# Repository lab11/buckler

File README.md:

Berkeley Buckler-ext
================

This is a fork of https://github.com/lab11/buckler

It changes Board makefiles to support https://github.com/gestalt-arch/gestalt-arch

It also extends the i2c implementation to support a lidar sensor via SC16IS750 I2C/SPI to UART Bridge Module from sandboxelectronics.com

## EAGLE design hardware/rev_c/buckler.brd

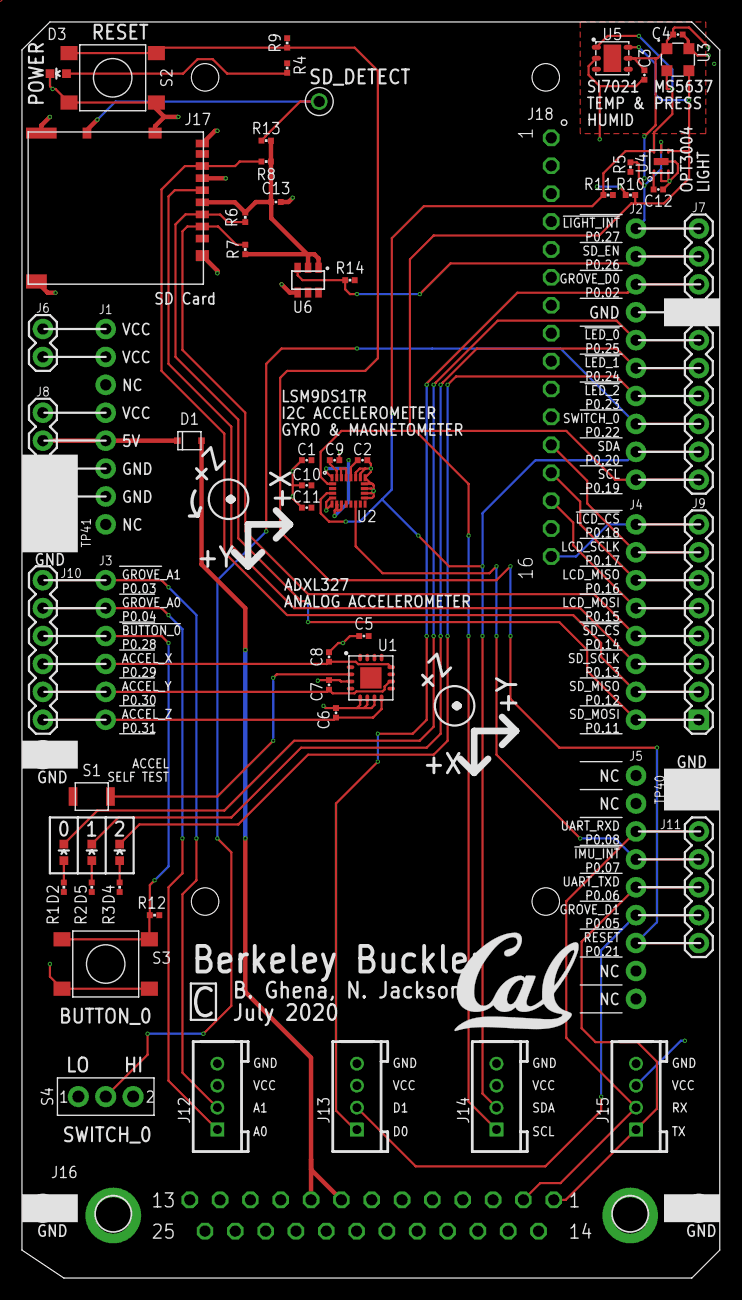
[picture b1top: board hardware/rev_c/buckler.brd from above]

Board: 2 copper layers, 63.5 x 114.3 mm, 63 parts (0 on the bottom side), 41 nets.

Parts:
C1, C2: 10nF; 0402_CAP
C3, C4, C5, C6, C7, C8, C9, C10, C11, C12: 100nF; 0402_CAP
C13: 4.7uF; 0402_CAP
D1: SOD323
D2: RED; LED-0603
D3: GREEN; LED-0603
D4: BLUE; LED-0603
D5: YELLOW; LED-0603
J1: NRF52832DK_SHIELD
J6: 1X02
J7: M10"; 1X10
J8: 1X04
J9: 1X08
J10: 1X06
J11: 1X05
J12, J13, J14, J15: HW4-2.0
J16: DB25_5747846
J17: DM3AT-SF-PEJM5
J18: NHD-0216KZWSERIAL; NHD-0216KZW
R1, R2, R3, R4: 1k; 0402_RES
R5, R6, R7, R8, R9, R10, R11, R12: 10k; 0402_RES
R13, R14: 100k; 0402_RES
S1: B3U-1000P
S2, S3: PTS645SM43SMTR92; PTS645
S4: TE_SSA12/SPDT
TP35, TP36, TP37, TP38: TEST_POINT_0.040IN; TESTPOINT_0.040IN
TP40, TP41: TEST_POINT_0.078IN; TESTPOINT_0.078IN
U1: ADXL327; LFCSP-16
U2: LSM9DS1TR; LGA-24_3X3P5X1_STM
U3: MS5637-02BA03; 4-SMD
U4: OPT3004DNPR; DNP0006A
U5: SI7021-A20-GM1; DFN-6/3MM
U6: SIP32510; TSOT23-6
U$5: UCB_CAL_350MIL

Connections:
5V_IN: D1.P$2, J16.8, J16.9
!BUTTON_0: J1.P0.28, J10.4, R12.1, S3.1, S3.2
!IMU_INTERRUPT: J1.P0.07, J11.4, U2.11
!LCD_CS: J1.P0.18, J9.8, J18.16
!LED_0: D2.C, J1.P0.25, J7.5
!LED_1: D5.C, J1.P0.24, J7.6
!LED_2: D4.C, J1.P0.23, J7.7
!LIGHT_INTERRUPT: J1.P0.27, J7.1, R5.1, U4.5
!RESET: J1.P0.21, J11.1, R9.1, S2.1, S2.2
!SD_CS: J1.P0.14, J9.4, J17.2, R7.1
!SD_DETECT: J17.A, R13.1, TP38.TESTPOINT
+3V3: C1.2, C3.1, C4.1, C5.1, C10.2, C11.2, C12.1, J1.3.3V@0, J1.3.3V@1, J1.3.3V@2, J6.1, J6.2, J8.4, J12.3, J13.3, J14.3, J15.3, J18.2, R1.1, R2.1, R3.1, R4.1, R5.2, R9.2, R10.2, R11.2, R12.2, R14.2, S1.2, S4.2, U1.14, U1.15, U2.1, U2.3, U2.7, U2.8, U2.22, U2.23, U3.1, U4.1, U5.5, U6.5, U6.6
+5V: D1.P$1, J1.5V, J8.3
ANALOG_ACCEL_X: C8.1, J1.P0.29, J10.3, U1.12
ANALOG_ACCEL_Y: C7.1, J1.P0.30, J10.2, U1.10
ANALOG_ACCEL_Z: C6.1, J1.P0.31, J10.1, U1.8
GND: C1.1, C2.1, C3.2, C4.2, C5.2, C6.2, C7.2, C8.2, C9.2, C10.1, C11.1, C12.2, C13.2, D3.C, J1.GND@0, J1.GND@1, J1.GND@2, J7.4, J8.1, J8.2, J12.4, J13.4, J14.4, J15.4, J16.6, J16.16, J16.20, J16.21, J16.24, J16.25, J17.6, J17.B, J17.MOUNT0, J17.MOUNT1, J17.MOUNT2, J17.MOUNT3, J18.1, S2.3, S2.4, S3.3, S3.4, S4.1, TP35.TESTPOINT, TP36.TESTPOINT, TP37.TESTPOINT, TP40.1, TP41.1, U1.3, U1.5, U1.6, U1.7, U2.5, U2.6, U2.14, U2.15, U2.16, U2.17, U2.18, U2.19, U2.20, U3.4, U4.2, U4.3, U4.7, U5.2, U6.4
GROVE_A0: J1.P0.04, J10.5, J12.1
GROVE_A1: J1.P0.03, J10.6, J12.2
GROVE_D0: J1.P0.02, J7.3, J13.1
GROVE_D1: J1.P0.05, J11.2, J13.2
LCD_MISO: J1.P0.16, J9.6, J18.13
LCD_MOSI: J1.P0.15, J9.5, J18.14
LCD_SCLK: J1.P0.17, J9.7, J18.12
unnamed: C9.1, U2.24
unnamed: D3.A, R4.2
unnamed: D4.A, R3.2
unnamed: D5.A, R2.2
unnamed: C2.2, U2.21
unnamed: S1.1, U1.2
unnamed: C13.1, J17.4, R6.2, R7.2, R8.2, R13.2, U6.1, U6.2
unnamed: D2.A, R1.2
SD_ENABLE: J1.P0.26, J7.2, R14.1, U6.3
SD_MISO: J1.P0.12, J9.2, J17.7, R8.1
SD_MOSI: J1.P0.11, J9.1, J17.3, R6.1
SD_SCLK: J1.P0.13, J9.3, J17.5
SENSORS_SCL: J1.P0.19, J7.10, J14.1, R10.1, U2.2, U3.3, U4.4, U5.6
SENSORS_SDA: J1.P0.20, J7.9, J14.2, R11.1, U2.4, U3.2, U4.6, U5.1
SWITCH_0: J1.P0.22, J7.8, S4.IN
UART_RX: J1.P0.08, J11.5, J15.2, J16.2
UART_TX: J1.P0.06, J11.3, J15.1, J16.1

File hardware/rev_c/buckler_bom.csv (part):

# Bill of Materials,,,,,,,,,,,,,,,,,,,,,,,,,,,,,,,,,,,,,,,,,,,,,,,,,,,,,,,,,,,,,,,,,,,,,,,,,,,,,,,,,,,,,,,,,,,,,,,,,,,,,,,,,,,,,,,,,,,,,,,,,,,,,,,,,,,,,,,,,,,,,,,,,,,,,,,,,,,,,,,,,,,,,,,,,,,,,,,,,,,,,,,,,,,,,,,,,,,,,,,,,,,,,,,,,,,,,,,,,,,,,,,,,,,,,,,,,,,,,,,,,,,,,,,,,,,,,,,,,,,,,,,,,,,,,,,,,,,,,,,,,,,,,,,,,,,,,,,,,,,,,,,,,,,,,,,,,,,,,,,,,,,,,,,,,,,,,,,,,,,,,,,,,,,,,,,,,,,,,,,,,,,,,,,,,,,,,,,,,,,,,,,,,,,,,,,,,,,,,,,,,,,,,,,,,,,,,,,,,,,,,,,,,,,,,,,,,,,,,,,,,,,,,,,,,,,,,,,,,,,,,,,,,,,,,,,,,,,,,,,,,,,,,,,,,,,,,,,,,,,,,,,,,,,,,,,,,,,,,,,,,,,,,,,,,,,,,,,,,,,,,,,,,,,,,,,,,,,,,,,,,,,,,,,,,,,,,,,,,,,,,,,,,,,,,,,,,,,,,,,,,,,,,,,,,,,,,,,,,,,,,,,,,,,,,,,,,,,,,,,,,,,,,,,,,,,,,,,,,,,,,,,,,,,,,,,,,,,,,,,,,,,,,,,,,,,,,,,,,,,,,,,,,,,,,,,,,,,,,,,,,,,,,,,,,,,,,,,,,,,,,,,,,,,,,,,,,,,,,,,,,,,,,,,,,,,,,,,,,,,,,,,,,,,,,,,,,,,,,,,,,,,,,,,,,,,,,,,,,,,,,,,,,,,,,,,,,,,,,,,,,,,,,,,,,,,,,,,,,,,,,,,,,,,,,,,,,,,,,,,,,,,,,,,,,,,,,,,,,,,,,,,,,,,,,,,,,,,,,,,,,,,,,,,,,,,,,,,,,,,,,,,,,,,,,,,,,,,,,,,,,,,,,,,,,,,,,,,,,,,,,,,,,,,,,,,,,,,,,,,,,,,,,,,,,,,,,,,,,,,,,,,
# Converted from {},,,,,,,,,,,,,,,,,,,,,,,,,,,,,,,,,,,,,,,,,,,,,,,,,,,,,,,,,,,,,,,,,,,,,,,,,,,,,,,,,,,,,,,,,,,,,,,,,,,,,,,,,,,,,,,,,,,,,,,,,,,,,,,,,,,,,,,,,,,,,,,,,,,,,,,,,,,,,,,,,,,,,,,,,,,,,,,,,,,,,,,,,,,,,,,,,,,,,,,,,,,,,,,,,,,,,,,,,,,,,,,,,,,,,,,,,,,,,,,,,,,,,,,,,,,,,,,,,,,,,,,,,,,,,,,,,,,,,,,,,,,,,,,,,,,,,,,,,,,,,,,,,,,,,,,,,,,,,,,,,,,,,,,,,,,,,,,,,,,,,,,,,,,,,,,,,,,,,,,,,,,,,,,,,,,,,,,,,,,,,,,,,,,,,,,,,,,,,,,,,,,,,,,,,,,,,,,,,,,,,,,,,,,,,,,,,,,,,,,,,,,,,,,,,,,,,,,,,,,,,,,,,,,,,,,,,,,,,,,,,,,,,,,,,,,,,,,,,,,,,,,,,,,,,,,,,,,,,,,,,,,,,,,,,,,,,,,,,,,,,,,,,,,,,,,,,,,,,,,,,,,,,,,,,,,,,,,,,,,,,,,,,,,,,,,,,,,,,,,,,,,,,,,,,,,,,,,,,,,,,,,,,,,,,,,,,,,,,,,,,,,,,,,,,,,,,,,,,,,,,,,,,,,,,,,,,,,,,,,,,,,,,,,,,,,,,,,,,,,,,,,,,,,,,,,,,,,,,,,,,,,,,,,,,,,,,,,,,,,,,,,,,,,,,,,,,,,,,,,,,,,,,,,,,,,,,,,,,,,,,,,,,,,,,,,,,,,,,,,,,,,,,,,,,,,,,,,,,,,,,,,,,,,,,,,,,,,,,,,,,,,,,,,,,,,,,,,,,,,,,,,,,,,,,,,,,,,,,,,,,,,,,,,,,,,,,,,,,,,,,,,,,,,,,,,,,,,,,,,,,,,,,,,,,,,,,,,,,,,,,,,,,,,,,,,,,,,,,,,,,,,,,,,,,,,,,,,,,,,,,,,,,,,,,,,,,,,,,,,,,,,,,,,,,,,,,,,,,,,,,,,
# Generated by bom_to_text.py,,,,,,,,,,,,,,,,,,,,,,,,,,,,,,,,,,,,,,,,,,,,,,,,,,,,,,,,,,,,,,,,,,,,,,,,,,,,,,,,,,,,,,,,,,,,,,,,,,,,,,,,,,,,,,,,,,,,,,,,,,,,,,,,,,,,,,,,,,,,,,,,,,,,,,,,,,,,,,,,,,,,,,,,,,,,,,,,,,,,,,,,,,,,,,,,,,,,,,,,,,,,,,,,,,,,,,,,,,,,,,,,,,,,,,,,,,,,,,,,,,,,,,,,,,,,,,,,,,,,,,,,,,,,,,,,,,,,,,,,,,,,,,,,,,,,,,,,,,,,,,,,,,,,,,,,,,,,,,,,,,,,,,,,,,,,,,,,,,,,,,,,,,,,,,,,,,,,,,,,,,,,,,,,,,,,,,,,,,,,,,,,,,,,,,,,,,,,,,,,,,,,,,,,,,,,,,,,,,,,,,,,,,,,,,,,,,,,,,,,,,,,,,,,,,,,,,,,,,,,,,,,,,,,,,,,,,,,,,,,,,,,,,,,,,,,,,,,,,,,,,,,,,,,,,,,,,,,,,,,,,,,,,,,,,,,,,,,,,,,,,,,,,,,,,,,,,,,,,,,,,,,,,,,,,,,,,,,,,,,,,,,,,,,,,,,,,,,,,,,,,,,,,,,,,,,,,,,,,,,,,,,,,,,,,,,,,,,,,,,,,,,,,,,,,,,,,,,,,,,,,,,,,,,,,,,,,,,,,,,,,,,,,,,,,,,,,,,,,,,,,,,,,,,,,,,,,,,,,,,,,,,,,,,,,,,,,,,,,,,,,,,,,,,,,,,,,,,,,,,,,,,,,,,,,,,,,,,,,,,,,,,,,,,,,,,,,,,,,,,,,,,,,,,,,,,,,,,,,,,,,,,,,,,,,,,,,,,,,,,,,,,,,,,,,,,,,,,,,,,,,,,,,,,,,,,,,,,,,,,,,,,,,,,,,,,,,,,,,,,,,,,,,,,,,,,,,,,,,,,,,,,,,,,,,,,,,,,,,,,,,,,,,,,,,,,,,,,,,,,,,,,,,,,,,,,,,,,,,,,,,,,,,,,,,,,,,,,,,,,,,,,,,,,,,,,,,,,,,,,,,,
#,,,,,,,,,,,,,,,,,,,,,,,,,,,,,,,,,,,,,,,,,,,,,,,,,,,,,,,,,,,,,,,,,,,,,,,,,,,,,,,,,,,,,,,,,,,,,,,,,,,,,,,,,,,,,,,,,,,,,,,,,,,,,,,,,,,,,,,,,,,,,,,,,,,,,,,,,,,,,,,,,,,,,,,,,,,,,,,,,,,,,,,,,,,,,,,,,,,,,,,,,,,,,,,,,,,,,,,,,,,,,,,,,,,,,,,,,,,,,,,,,,,,,,,,,,,,,,,,,,,,,,,,,,,,,,,,,,,,,,,,,,,,,,,,,,,,,,,,,,,,,,,,,,,,,,,,,,,,,,,,,,,,,,,,,,,,,,,,,,,,,,,,,,,,,,,,,,,,,,,,,,,,,,,,,,,,,,,,,,,,,,,,,,,,,,,,,,,,,,,,,,,,,,,,,,,,,,,,,,,,,,,,,,,,,,,,,,,,,,,,,,,,,,,,,,,,,,,,,,,,,,,,,,,,,,,,,,,,,,,,,,,,,,,,,,,,,,,,,,,,,,,,,,,,,,,,,,,,,,,,,,,,,,,,,,,,,,,,,,,,,,,,,,,,,,,,,,,,,,,,,,,,,,,,,,,,,,,,,,,,,,,,,,,,,,,,,,,,,,,,,,,,,,,,,,,,,,,,,,,,,,,,,,,,,,,,,,,,,,,,,,,,,,,,,,,,,,,,,,,,,,,,,,,,,,,,,,,,,,,,,,,,,,,,,,,,,,,,,,,,,,,,,,,,,,,,,,,,,,,,,,,,,,,,,,,,,,,,,,,,,,,,,,,,,,,,,,,,,,,,,,,,,,,,,,,,,,,,,,,,,,,,,,,,,,,,,,,,,,,,,,,,,,,,,,,,,,,,,,,,,,,,,,,,,,,,,,,,,,,,,,,,,,,,,,,,,,,,,,,,,,,,,,,,,,,,,,,,,,,,,,,,,,,,,,,,,,,,,,,,,,,,,,,,,,,,,,,,,,,,,,,,,,,,,,,,,,,,,,,,,,,,,,,,,,,,,,,,,,,,,,,,,,,,,,,,,,,,,,,,,,,,,,,,,,,,,,,,,,,,,,,,,,,,,,,,,,,,,,,,,,,
,,,,,,,,,,,,,,,,,,,,,,,,,,,,,,,,,,,,,,,,,,,,,,,,,,,,,,,,,,,,,,,,,,,,,,,,,,,,,,,,,,,,,,,,,,,,,,,,,,,,,,,,,,,,,,,,,,,,,,,,,,,,,,,,,,,,,,,,,,,,,,,,,,,,,,,,,,,,,,,,,,,,,,,,,,,,,,,,,,,,,,,,,,,,,,,,,,,,,,,,,,,,,,,,,,,,,,,,,,,,,,,,,,,,,,,,,,,,,,,,,,,,,,,,,,,,,,,,,,,,,,,,,,,,,,,,,,,,,,,,,,,,,,,,,,,,,,,,,,,,,,,,,,,,,,,,,,,,,,,,,,,,,,,,,,,,,,,,,,,,,,,,,,,,,,,,,,,,,,,,,,,,,,,,,,,,,,,,,,,,,,,,,,,,,,,,,,,,,,,,,,,,,,,,,,,,,,,,,,,,,,,,,,,,,,,,,,,,,,,,,,,,,,,,,,,,,,,,,,,,,,,,,,,,,,,,,,,,,,,,,,,,,,,,,,,,,,,,,,,,,,,,,,,,,,,,,,,,,,,,,,,,,,,,,,,,,,,,,,,,,,,,,,,,,,,,,,,,,,,,,,,,,,,,,,,,,,,,,,,,,,,,,,,,,,,,,,,,,,,,,,,,,,,,,,,,,,,,,,,,,,,,,,,,,,,,,,,,,,,,,,,,,,,,,,,,,,,,,,,,,,,,,,,,,,,,,,,,,,,,,,,,,,,,,,,,,,,,,,,,,,,,,,,,,,,,,,,,,,,,,,,,,,,,,,,,,,,,,,,,,,,,,,,,,,,,,,,,,,,,,,,,,,,,,,,,,,,,,,,,,,,,,,,,,,,,,,,,,,,,,,,,,,,,,,,,,,,,,,,,,,,,,,,,,,,,,,,,,,,,,,,,,,,,,,,,,,,,,,,,,,,,,,,,,,,,,,,,,,,,,,,,,,,,,,,,,,,,,,,,,,,,,,,,,,,,,,,,,,,,,,,,,,,,,,,,,,,,,,,,,,,,,,,,,,,,,,,,,,,,,,,,,,,,,,,,,,,,,,,,,,,,,,,,,,,,,,,,,,,,,,,,,,,,,,,,,,,,,,,,,,,
Qty,Value,Device,Package,Parts,Description,DESCRIPTION,DIGIKEY,MANUFACTURER,MOUSER,MPN,,,,,,,,,,,,,,,,,,,,,,,,,,,,,,,,,,,,,,,,,,,,,,,,,,,,,,,,,,,,,,,,,,,,,,,,,,,,,,,,,,,,,,,,,,,,,,,,,,,,,,,,,,,,,,,,,,,,,,,,,,,,,,,,,,,,,,,,,,,,,,,,,,,,,,,,,,,,,,,,,,,,,,,,,,,,,,,,,,,,,,,,,,,,,,,,,,,,,,,,,,,,,,,,,,,,,,,,,,,,,,,,,,,,,,,,,,,,,,,,,,,,,,,,,,,,,,,,,,,,,,,,,,,,,,,,,,,,,,,,,,,,,,,,,,,,,,,,,,,,,,,,,,,,,,,,,,,,,,,,,,,,,,,,,,,,,,,,,,,,,,,,,,,,,,,,,,,,,,,,,,,,,,,,,,,,,,,,,,,,,,,,,,,,,,,,,,,,,,,,,,,,,,,,,,,,,,,,,,,,,,,,,,,,,,,,,,,,,,,,,,,,,,,,,,,,,,,,,,,,,,,,,,,,,,,,,,,,,,,,,,,,,,,,,,,,,,,,,,,,,,,,,,,,,,,,,,,,,,,,,,,,,,,,,,,,,,,,,,,,,,,,,,,,,,,,,,,,,,,,,,,,,,,,,,,,,,,,,,,,,,,,,,,,,,,,,,,,,,,,,,,,,,,,,,,,,,,,,,,,,,,,,,,,,,,,,,,,,,,,,,,,,,,,,,,,,,,,,,,,,,,,,,,,,,,,,,,,,,,,,,,,,,,,,,,,,,,,,,,,,,,,,,,,,,,,,,,,,,,,,,,,,,,,,,,,,,,,,,,,,,,,,,,,,,,,,,,,,,,,,,,,,,,,,,,,,,,,,,,,,,,,,,,,,,,,,,,,,,,,,,,,,,,,,,,,,,,,,,,,,,,,,,,,,,,,,,,,,,,,,,,,,,,,,,,,,,,,,,,,,,,,,,,,,,,,,,,,,,,,,,,,,,,,,,,,,,,,,,,,,,,,,,,,,,,,,,,,,,,,,,,,,,,,,,,,,,,,,,,,,,,,,,,,,,,,,,,,,,,,,,,,,,,,,,,,,,,,,,,,,,,,,,,,,,,,,,,,,,,,,,,,,,,,,,,,,
1,,DIODE_SCHOTTKYSOD323,SOD323,D1,,DIODE SCHOTTKY 30V 500MA SOD323,B0530WS-FDICT-ND,Diodes Incorporated,,B0530WS-7-F,,,,,,,,,,,,,,,,,,,,,,,,,,,,,,,,,,,,,,,,,,,,,,,,,,,,,,,,,,,,,,,,,,,,,,,,,,,,,,,,,,,,,,,,,,,,,,,,,,,,,,,,,,,,,,,,,,,,,,,,,,,,,,,,,,,,,,,,,,,,,,,,,,,,,,,,,,,,,,,,,,,,,,,,,,,,,,,,,,,,,,,,,,,,,,,,,,,,,,,,,,,,,,,,,,,,,,,,,,,,,,,,,,,,,,,,,,,,,,,,,,,,,,,,,,,,,,,,,,,,,,,,,,,,,,,,,,,,,,,,,,,,,,,,,,,,,,,,,,,,,,,,,,,,,,,,,,,,,,,,,,,,,,,,,,,,,,,,,,,,,,,,,,,,,,,,,,,,,,,,,,,,,,,,,,,,,,,,,,,,,,,,,,,,,,,,,,,,,,,,,,,,,,,,,,,,,,,,,,,,,,,,,,,,,,,,,,,,,,,,,,,,,,,,,,,,,,,,,,,,,,,,,,,,,,,,,,,,,,,,,,,,,,,,,,,,,,,,,,,,,,,,,,,,,,,,,,,,,,,,,,,,,,,,,,,,,,,,,,,,,,,,,,,,,,,,,,,,,,,,,,,,,,,,,,,,,,,,,,,,,,,,,,,,,,,,,,,,,,,,,,,,,,,,,,,,,,,,,,,,,,,,,,,,,,,,,,,,,,,,,,,,,,,,,,,,,,,,,,,,,,,,,,,,,,,,,,,,,,,,,,,,,,,,,,,,,,,,,,,,,,,,,,,,,,,,,,,,,,,,,,,,,,,,,,,,,,,,,,,,,,,,,,,,,,,,,,,,,,,,,,,,,,,,,,,,,,,,,,,,,,,,,,,,,,,,,,,,,,,,,,,,,,,,,,,,,,,,,,,,,,,,,,,,,,,,,,,,,,,,,,,,,,,,,,,,,,,,,,,,,,,,,,,,,,,,,,,,,,,,,,,,,,,,,,,,,,,,,,,,,,,,,,,,,,,,,,,,,,,,,,,,,,,,,,,,,,,,,,,,,,,,,,,,,,,,,,,,,,,,,,,,,,,,,,,,,,,,,,,,,,,,,,,,,,,,,,,,,,,,,,,,,,,,,,,,,
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
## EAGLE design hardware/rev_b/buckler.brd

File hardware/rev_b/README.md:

Hardware Files
==============

The Berkeley Buckler was created in
[Eagle](https://www.autodesk.com/products/eagle/overview) and the `buckler.sch`
and `buckler.brd` files are Eagle schematic and board files respectively.
Schematic and board files can be viewed without Eagle in `buckler.pdf`.
`buckler_bom.xlsx` is the Bill of Materials (list of parts). It is also
provided as `txt` and `csv` files for convenience.

## Changes from prior revision
 * Change base board from the nRF52840DK to the nRF52DK (based on the nRF52832) due to availability
     * Reduced number of buttons, switches, and grove headers to deal with reduced number of pins
     * Removed connection to SD card detect signal to deal with reduced number of pins
     * Re-mapped signals to development kit pins
 * Made text bigger and added more test points
 * Shrunk board size a little

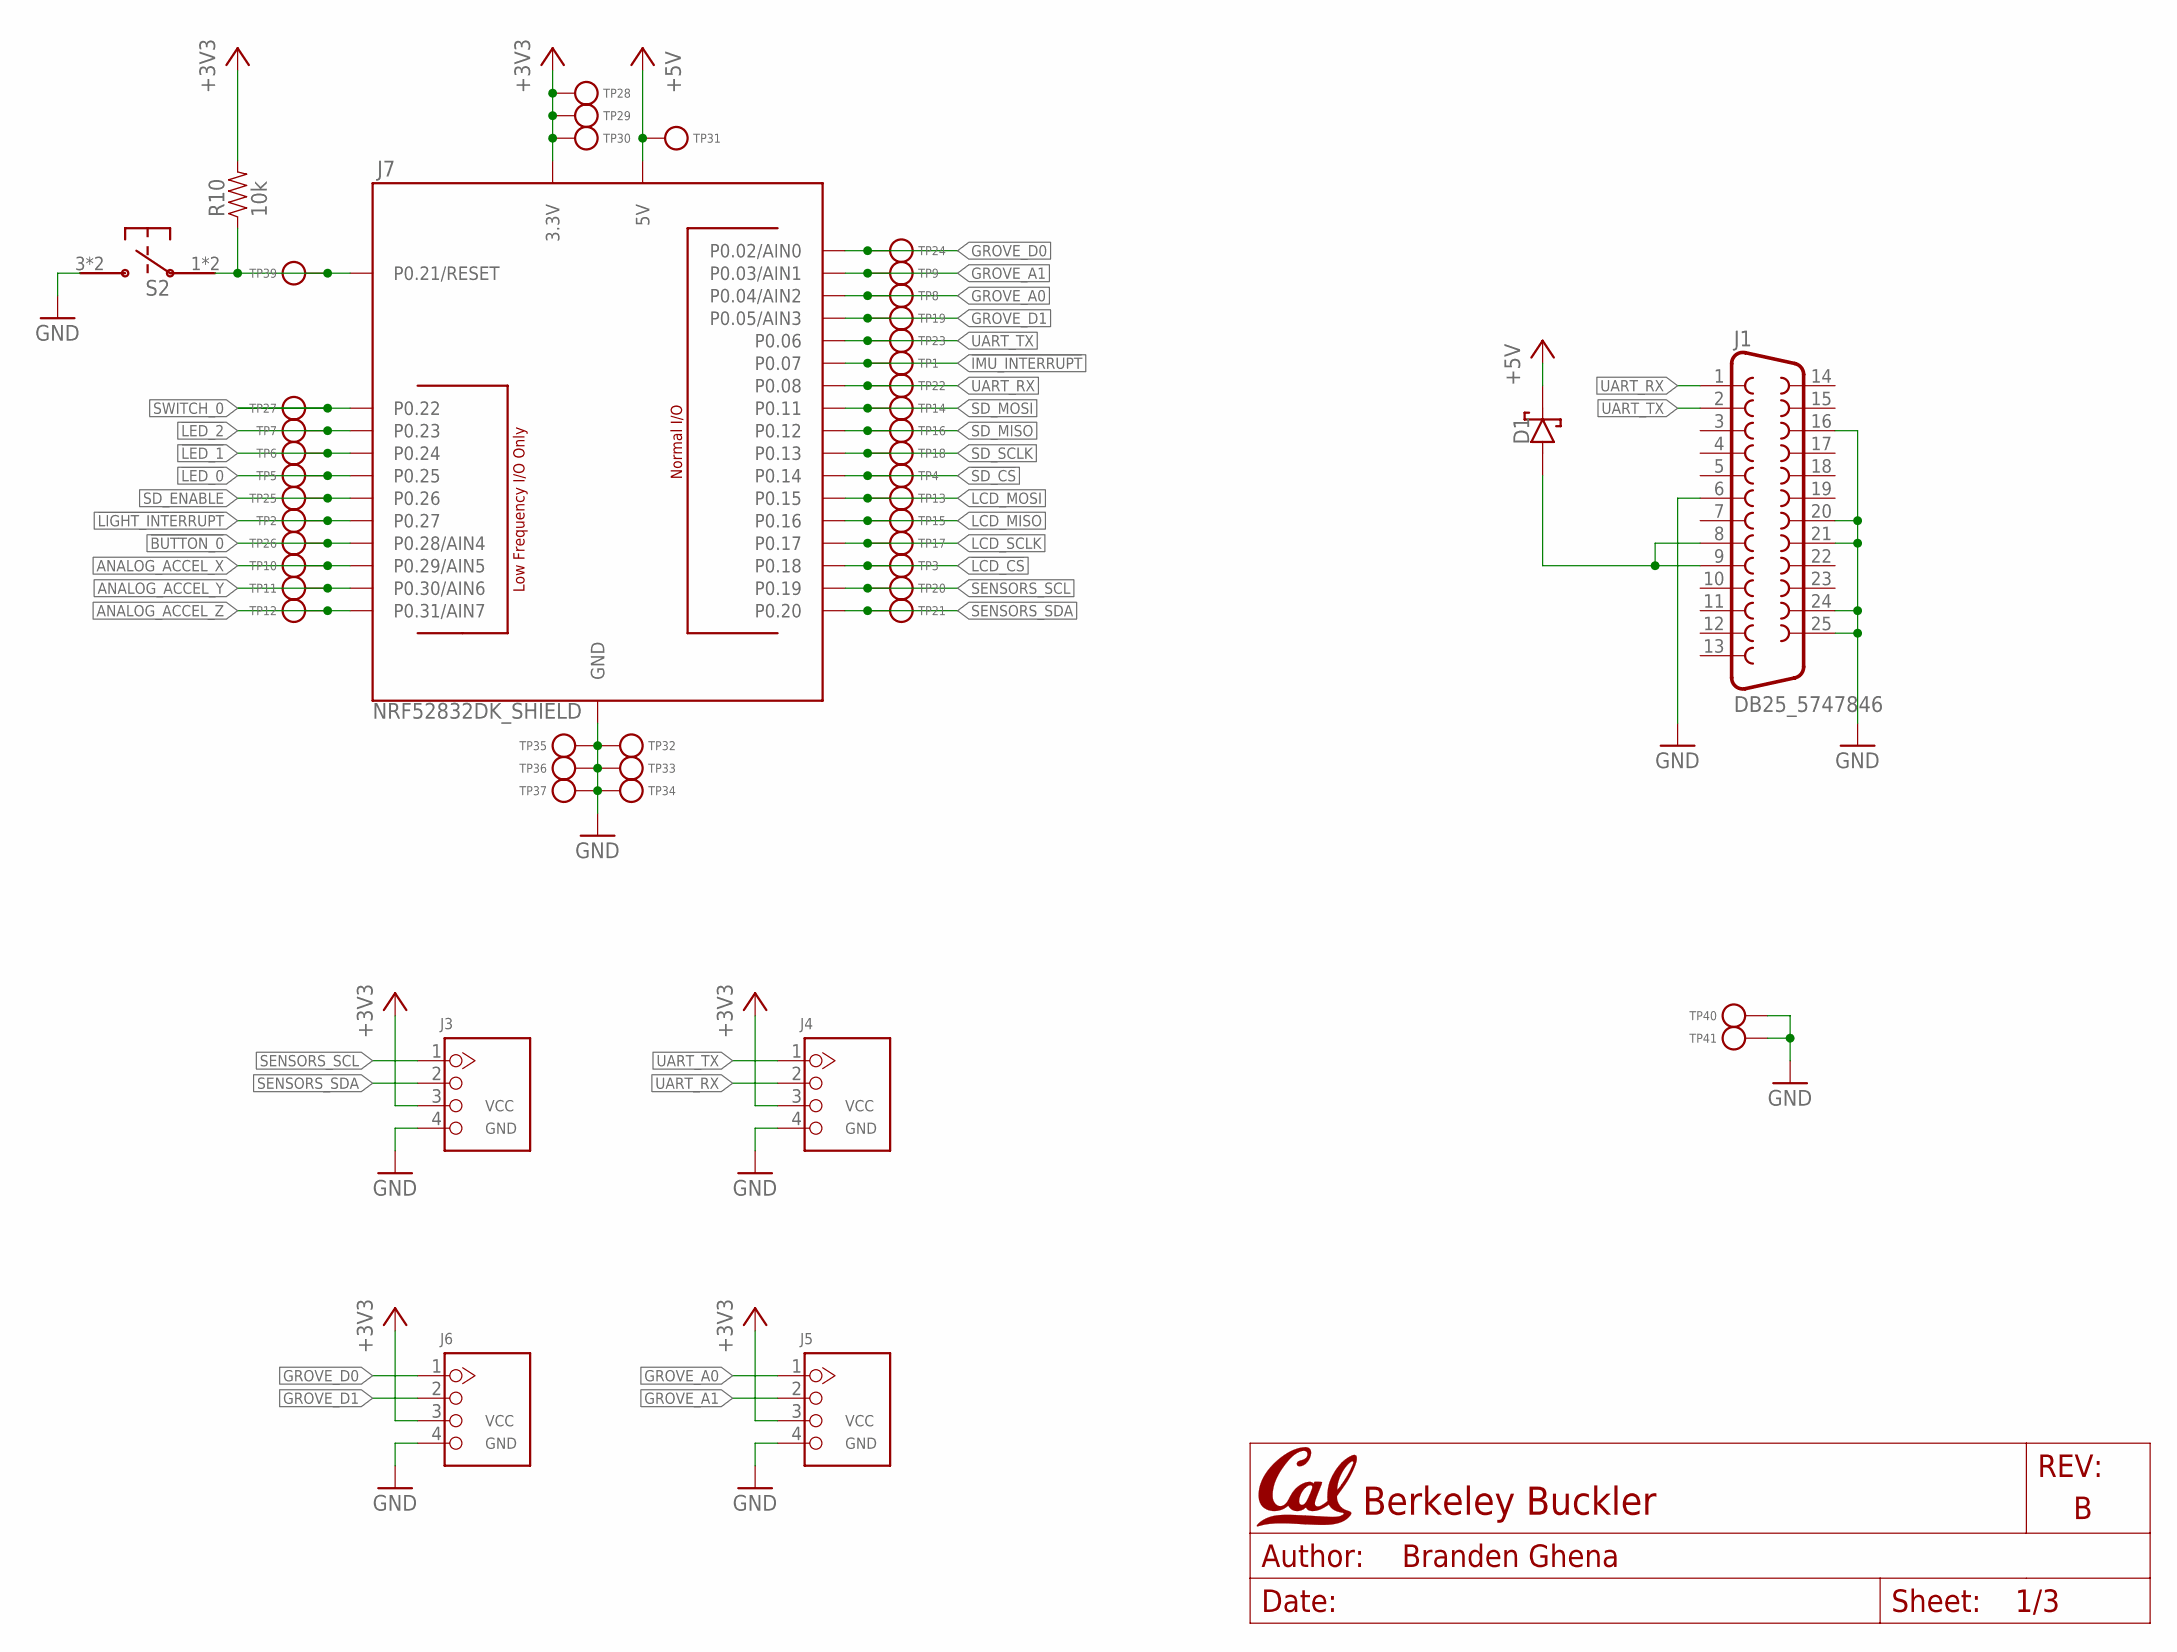
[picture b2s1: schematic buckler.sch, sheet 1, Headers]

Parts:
D1: DIODE_SCHOTTKYSOD323; SOD323; MPN B0530WS-7-F; DIGIKEY B0530WS-FDICT-ND
J1: DB25_5747846; MPN 5747846-4
J3, J4, J5, J6: GROVE-CONNECTOR-DIP(4P-2.0); HW4-2.0; MPN 110990030; MOUSER 713-110990030
J7: NRF52832DK_SHIELD; DIGIKEY1 S1011EC-10-ND
R10: 10k; 0402_RES; MPN RC1005F103CS; DIGIKEY 1276-3431-1-ND
S2: PTS645SM43SMTR92; PTS645; MPN PTS645SM43SMTR92 LFS
TP1, TP2, TP3, TP4, TP5, TP6, TP7, TP8, TP9, TP10, TP11, TP12, TP13, TP14, TP15, TP16, TP17, TP18, TP19, TP20, TP21, TP22, TP23, TP24, TP25, TP26, TP27, TP28, TP29, TP30, TP31, TP32, TP33, TP34, TP35, TP36, TP37, TP39: TEST_POINT_0.040IN; TESTPOINT_0.040IN
TP40, TP41: TEST_POINT_0.078IN; TESTPOINT_0.078IN; MPN 1520-2; DIGIKEY 36-1520-2-ND

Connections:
5V_IN: D1.P$2 (ANODE), J1.8, J1.9
!BUTTON_0: J7.P0.28 (P0.28/AIN4), TP26.TESTPOINT; also elsewhere on the board
!IMU_INTERRUPT: J7.P0.07, TP1.TESTPOINT; also elsewhere on the board
!LCD_CS: J7.P0.18, TP3.TESTPOINT; also elsewhere on the board
!LED_0: J7.P0.25, TP5.TESTPOINT; also elsewhere on the board
!LED_1: J7.P0.24, TP6.TESTPOINT; also elsewhere on the board
!LED_2: J7.P0.23, TP7.TESTPOINT; also elsewhere on the board
!LIGHT_INTERRUPT: J7.P0.27, TP2.TESTPOINT; also elsewhere on the board
!RESET: J7.P0.21 (P0.21/RESET), R10.1, S2.1, S2.2, TP39.TESTPOINT
!SD_CS: J7.P0.14, TP4.TESTPOINT; also elsewhere on the board
+3V3: J3.3, J4.3, J5.3, J6.3, J7.3.3V@0 (3.3V), J7.3.3V@1 (3.3V), J7.3.3V@2 (3.3V), R10.2, TP28.TESTPOINT, TP29.TESTPOINT, TP30.TESTPOINT; also elsewhere on the board
+5V: D1.P$1 (CATHODE), J7.5V, TP31.TESTPOINT
ANALOG_ACCEL_X: J7.P0.29 (P0.29/AIN5), TP10.TESTPOINT; also elsewhere on the board
ANALOG_ACCEL_Y: J7.P0.30 (P0.30/AIN6), TP11.TESTPOINT; also elsewhere on the board
ANALOG_ACCEL_Z: J7.P0.31 (P0.31/AIN7), TP12.TESTPOINT; also elsewhere on the board
GND: J1.6, J1.16, J1.20, J1.21, J1.24, J1.25, J3.4, J4.4, J5.4, J6.4, J7.GND@0 (GND), J7.GND@1 (GND), J7.GND@2 (GND), S2.3, S2.4, TP32.TESTPOINT, TP33.TESTPOINT, TP34.TESTPOINT, TP35.TESTPOINT, TP36.TESTPOINT, TP37.TESTPOINT, TP40.1, TP41.1; also elsewhere on the board
GROVE_A0: J5.1, J7.P0.04 (P0.04/AIN2), TP8.TESTPOINT
GROVE_A1: J5.2, J7.P0.03 (P0.03/AIN1), TP9.TESTPOINT
GROVE_D0: J6.1, J7.P0.02 (P0.02/AIN0), TP24.TESTPOINT
GROVE_D1: J6.2, J7.P0.05 (P0.05/AIN3), TP19.TESTPOINT
LCD_MISO: J7.P0.16, TP15.TESTPOINT; also elsewhere on the board
LCD_MOSI: J7.P0.15, TP13.TESTPOINT; also elsewhere on the board
LCD_SCLK: J7.P0.17, TP17.TESTPOINT; also elsewhere on the board
SD_ENABLE: J7.P0.26, TP25.TESTPOINT; also elsewhere on the board
SD_MISO: J7.P0.12, TP16.TESTPOINT; also elsewhere on the board
SD_MOSI: J7.P0.11, TP14.TESTPOINT; also elsewhere on the board
SD_SCLK: J7.P0.13, TP18.TESTPOINT; also elsewhere on the board
SENSORS_SCL: J3.1, J7.P0.19, TP20.TESTPOINT; also elsewhere on the board
SENSORS_SDA: J3.2, J7.P0.20, TP21.TESTPOINT; also elsewhere on the board
SWITCH_0: J7.P0.22, TP27.TESTPOINT; also elsewhere on the board
UART_RX: J1.1, J4.2, J7.P0.08, TP22.TESTPOINT
UART_TX: J1.2, J4.1, J7.P0.06, TP23.TESTPOINT

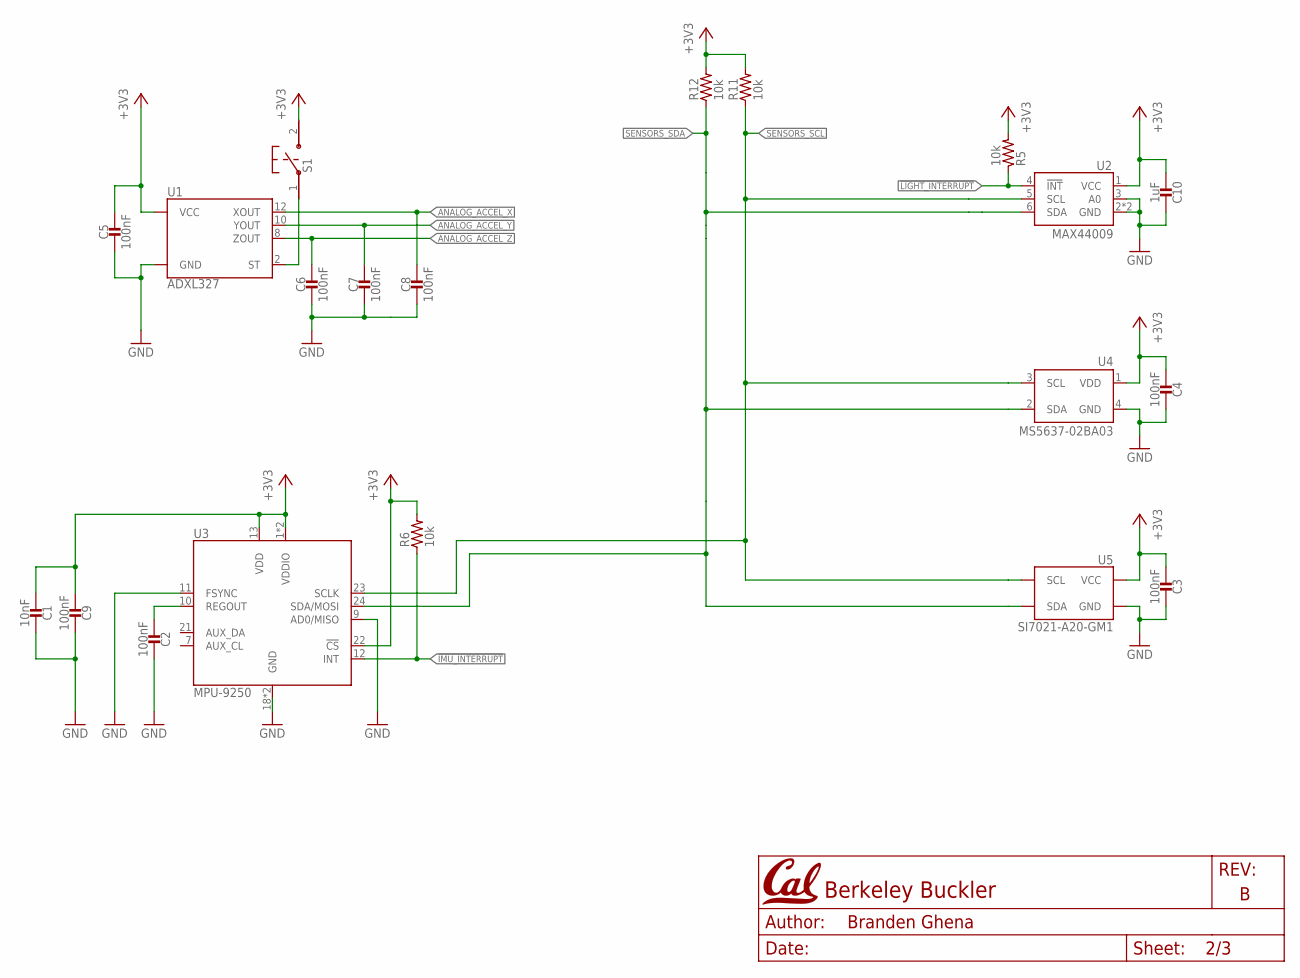
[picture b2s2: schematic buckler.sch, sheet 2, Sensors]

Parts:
C1: 10nF; 0402_CAP; MPN C0402C103J3RACTU; DIGIKEY 399-1279-1-ND
C2, C3, C4, C5, C6, C7, C8, C9: 100nF; 0402_CAP; MPN GCM155R71C104KA55D; DIGIKEY 490-4759-1-ND
C10: 1uF; 0402_CAP; MPN CL05X105KP5NNNC; DIGIKEY 1276-6805-1-ND
R5, R6, R11, R12: 10k; 0402_RES; MPN RC1005F103CS; DIGIKEY 1276-3431-1-ND
S1: B3U-1000P; MPN B3U-1000P
U1: ADXL327; LFCSP-16; MPN ADXL327BCPZ
U2: MAX44009; UDFN-6-EXPOSED
U3: MPU-9250; QFN-24/3MM; MPN MPU-9250
U4: MS5637-02BA03; 4-SMD
U5: SI7021-A20-GM1; DFN-6/3MM; MPN SI7021-A20-GM1

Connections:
!IMU_INTERRUPT: R6.1, U3.12 (INT); also elsewhere on the board
!LIGHT_INTERRUPT: R5.1, U2.4 (!INT); also elsewhere on the board
+3V3: C1.1, C3.1, C4.1, C5.1, C9.1, C10.1, R5.2, R6.2, R11.2, R12.2, S1.2, U1.14 (VCC), U1.15 (VCC), U2.1 (VCC), U3.1 (VDDIO), U3.8 (VDDIO), U3.13 (VDD), U3.22 (!CS), U4.1 (VDD), U5.5 (VCC); also elsewhere on the board
ANALOG_ACCEL_X: C8.1, U1.12 (XOUT); also elsewhere on the board
ANALOG_ACCEL_Y: C7.1, U1.10 (YOUT); also elsewhere on the board
ANALOG_ACCEL_Z: C6.1, U1.8 (ZOUT); also elsewhere on the board
GND: C1.2, C2.2, C3.2, C4.2, C5.2, C6.2, C7.2, C8.2, C9.2, C10.2, U1.3 (GND), U1.5 (GND), U1.6 (GND), U1.7 (GND), U2.2 (GND), U2.3 (A0), U2.EP (GND), U3.9 (AD0/MISO), U3.11 (FSYNC), U3.18 (GND), U3.20 (GND), U4.4 (GND), U5.2 (GND); also elsewhere on the board
unnamed: S1.1, U1.2 (ST)
unnamed: C2.1, U3.10 (REGOUT)
SENSORS_SCL: R11.1, U2.5 (SCL), U3.23 (SCLK), U4.3 (SCL), U5.6 (SCL); also elsewhere on the board
SENSORS_SDA: R12.1, U2.6 (SDA), U3.24 (SDA/MOSI), U4.2 (SDA), U5.1 (SDA); also elsewhere on the board

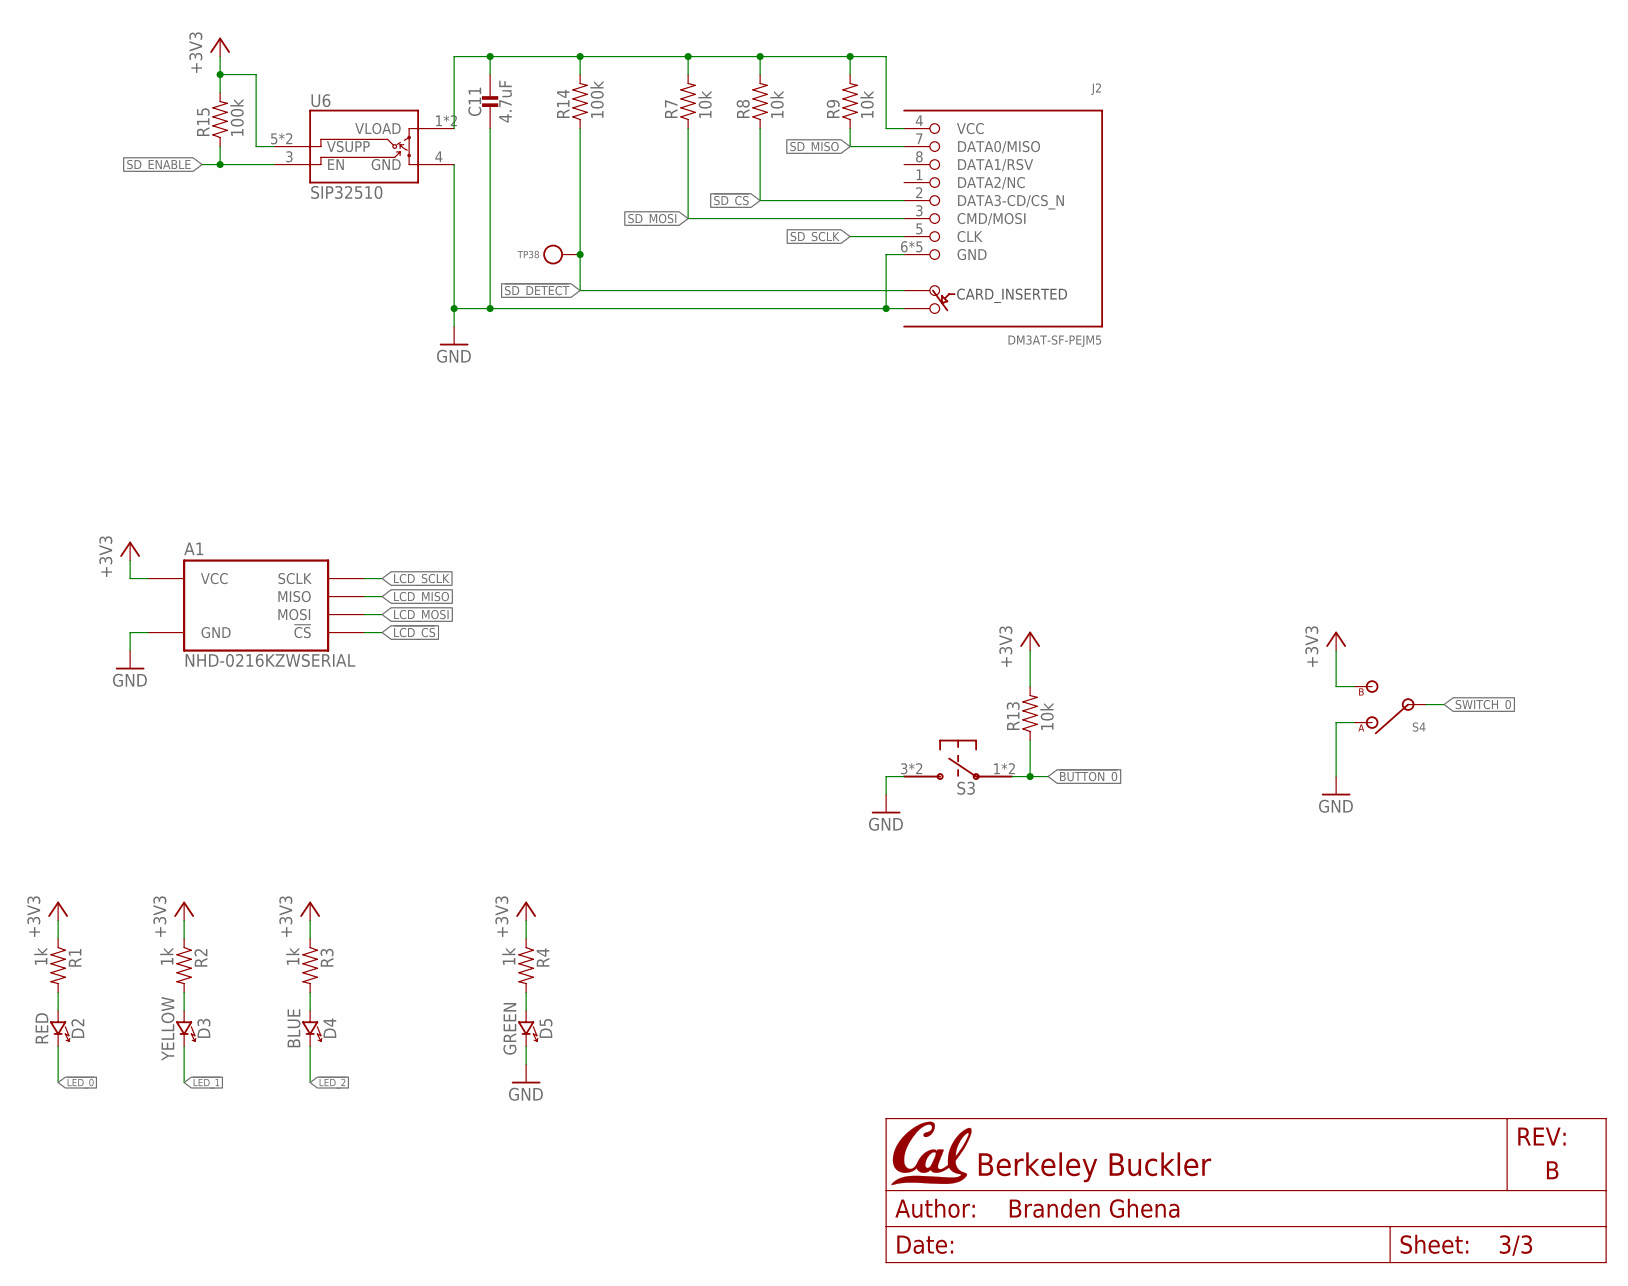
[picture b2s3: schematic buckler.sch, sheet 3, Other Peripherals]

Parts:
A1: NHD-0216KZWSERIAL; NHD-0216KZW; DIGIKEY1 NHD-0216KZW-AG5-ND
C11: 4.7uF; 0402_CAP; MPN CL05A475KP5NRNC; DIGIKEY 1276-1480-1-ND
D2: RED; LED-0603; MPN LTST-C190KRKT; DIGIKEY 160-1436-1-ND
D3: YELLOW; LED-0603; MPN LTST-C190KSKT; DIGIKEY 160-1437-1-ND
D4: BLUE; LED-0603; MPN LTST-C194TBKT; DIGIKEY 160-1837-1-ND
D5: GREEN; LED-0603; MPN LTST-C190KGKT; DIGIKEY 160-1435-1-ND
J2: DM3AT-SF-PEJM5
R1, R2, R3, R4: 1k; 0402_RES; MPN RMCF0402FT1K00; DIGIKEY RMCF0402FT1K00CT-ND
R7, R8, R9, R13: 10k; 0402_RES; MPN RC1005F103CS; DIGIKEY 1276-3431-1-ND
R14, R15: 100k; 0402_RES; MPN CRCW0402100KFKEDHP; DIGIKEY 541-100KYCT-ND
S3: PTS645SM43SMTR92; PTS645; MPN PTS645SM43SMTR92 LFS
S4: TE_SSA12/SPDT; MPN SSA12
TP38: TEST_POINT_0.040IN; TESTPOINT_0.040IN
U6: SIP32510; TSOT23-6

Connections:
!BUTTON_0: R13.1, S3.1, S3.2; also elsewhere on the board
!LCD_CS: A1.16 (!CS); also elsewhere on the board
!LED_0: D2.C (CATHODE); also elsewhere on the board
!LED_1: D3.C (CATHODE); also elsewhere on the board
!LED_2: D4.C (CATHODE); also elsewhere on the board
!SD_CS: J2.2 (DATA3-CD/CS_N), R8.1; also elsewhere on the board
!SD_DETECT: J2.A, R14.1, TP38.TESTPOINT
+3V3: A1.2 (VCC), R1.1, R2.1, R3.1, R4.1, R13.2, R15.2, S4.2 (B), U6.5 (VSUPP), U6.6 (VSUPP); also elsewhere on the board
GND: A1.1 (GND), C11.2, D5.C (CATHODE), J2.6 (GND), J2.B, J2.MOUNT0 (GND), J2.MOUNT1 (GND), J2.MOUNT2 (GND), J2.MOUNT3 (GND), S3.3, S3.4, S4.1 (A), U6.4 (GND); also elsewhere on the board
LCD_MISO: A1.13 (MISO); also elsewhere on the board
LCD_MOSI: A1.14 (MOSI); also elsewhere on the board
LCD_SCLK: A1.12 (SCLK); also elsewhere on the board
unnamed: D5.A (ANODE), R4.2
unnamed: D4.A (ANODE), R3.2
unnamed: D3.A (ANODE), R2.2
unnamed: C11.1, J2.4 (VCC), R7.2, R8.2, R9.2, R14.2, U6.1 (VLOAD), U6.2 (VLOAD)
unnamed: D2.A (ANODE), R1.2
SD_ENABLE: R15.1, U6.3 (EN); also elsewhere on the board
SD_MISO: J2.7 (DATA0/MISO), R9.1; also elsewhere on the board
SD_MOSI: J2.3 (CMD/MOSI), R7.1; also elsewhere on the board
SD_SCLK: J2.5 (CLK); also elsewhere on the board
SWITCH_0: S4.IN; also elsewhere on the board

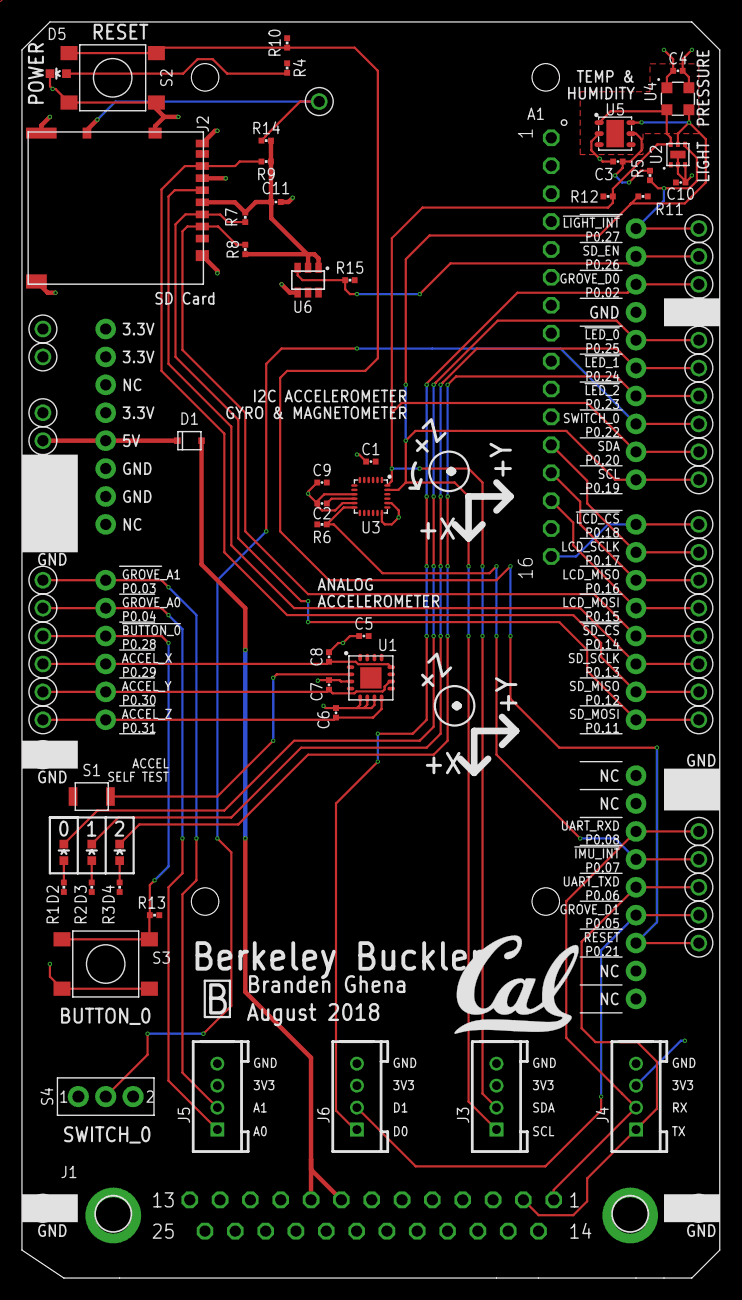
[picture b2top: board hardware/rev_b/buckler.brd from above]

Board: 2 copper layers, 63.5 x 114.3 mm, 91 parts (0 on the bottom side), 40 nets.

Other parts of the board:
U$5: UCB_CAL_350MIL

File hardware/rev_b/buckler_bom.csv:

# Bill of Materials,,,,,,,,,,,,,,,
# Converted from {},,,,,,,,,,,,,,,
# Generated by bom_to_text.py,,,,,,,,,,,,,,,
#,,,,,,,,,,,,,,,
,,,,,,,,,,,,,,,
Qty,Value,Device,Package,Parts,Description,DESCRIPTION,DIGIKEY,DIGIKEY1,DIGIKEY2,DIGIKEY3,DIGIKEY4,DIGIKEY5,MANUFACTURER,MOUSER,MPN
1,NHD-0216KZWSERIAL,NHD-0216KZWSERIAL,NHD-0216KZW,A1,,,,NHD-0216KZW-AG5-ND,952-3305-ND,952-1862-ND,,,,,
1,10nF,CAPACITOR0402_CAP,0402_CAP,C1,SMD Capacitor,CAP CER 10000PF 25V X7R 0402,399-1279-1-ND,,,,,,KEMET,,C0402C103J3RACTU
8,100nF,CAPACITOR0402_CAP,0402_CAP,"C2, C3, C4, C5, C6, C7, C8, C9",SMD Capacitor,CAP CER 0.1UF 16V X7R 0402,490-4759-1-ND,,,,,,Murata,,GCM155R71C104KA55D
1,1uF,CAPACITOR0402_CAP,0402_CAP,C10,SMD Capacitor,CAP CER 1UF 10V X6S 0402,1276-6805-1-ND,,,,,,Samsung Electro-Mechanics,,CL05X105KP5NNNC
1,4.7uF,CAPACITOR0402_CAP,0402_CAP,C11,SMD Capacitor,CAP CER 4.7UF 10V X5R 0402,1276-1480-1-ND,,,,,,Samsung Electro-Mechanics,,CL05A475KP5NRNC
1,,DIODE_SCHOTTKYSOD323,SOD323,D1,,DIODE SCHOTTKY 30V 500MA SOD323,B0530WS-FDICT-ND,,,,,,Diodes Incorporated,,B0530WS-7-F
1,RED,LED0603,LED-0603,D2,LED,LED RED CLEAR CHIP SMD,160-1436-1-ND,,,,,,Lite-On Inc.,,LTST-C190KRKT
1,YELLOW,LED0603,LED-0603,D3,LED,LED YELLOW CLEAR CHIP SMD,160-1437-1-ND,,,,,,Lite-On Inc.,,LTST-C190KSKT
1,BLUE,LED0603,LED-0603,D4,LED,LED BLUE CLEAR SMD,160-1837-1-ND,,,,,,Lite-On Inc.,,LTST-C194TBKT
1,GREEN,LED0603,LED-0603,D5,LED,LED GREEN CLEAR CHIP SMD,160-1435-1-ND,,,,,,Lite-On Inc.,,LTST-C190KGKT
1,DB25_5747846,DB25_5747846,DB25_5747846,J1,,CONN D-SUB RCPT 25POS R/A SOLDER,A32126-ND,,,,,,TE Connectivity AMP Connectors,,5747846-4
1,DM3AT-SF-PEJM5,DM3AT-SF-PEJM5,DM3AT-SF-PEJM5,J2,CONN MICRO SD R/A PUSH-PUSH SMD,CONN MICRO SD CARD PUSH-PUSH R/A,HR1964CT-ND,,,,,,Hirose Electric Co Ltd,,DM3AT-SF-PEJM5
4,DNP,GROVE-CONNECTOR-DIP(4P-2.0),HW4-2.0,"J3, J4, J5, J6",Grove - Universal 4 pin connector,Grove - Universal 4 pin connector,,,,,,,Seeed Studio,713-110990030,110990030
1,NRF52832DK_SHIELD,NRF52832DK_SHIELD,NRF52832DK_SHIELD,J7,Shield for the PCA10040 nRF52832 Development Kit,,,S1011EC-10-ND,S1011EC-08-ND,S1011EC-08-ND,S1011EC-06-ND,S1011EC-09-ND,Sullins Connector Solutions,,"PRPC010SAAN-RC, PRPC008SAAN-RC, PRPC008SAAN-RC, PRPC006SAAN-RC, PRPC009SAAN-RC"
4,1k,RESISTOR0402_RES,0402_RES,"R1, R2, R3, R4",Resistor,RES SMD 1K OHM 1% 1/16W 0402,RMCF0402FT1K00CT-ND,,,,,,Stackpole Electronics,,RMCF0402FT1K00
9,10k,RESISTOR0402_RES,0402_RES,"R5, R6, R7, R8, R9, R10, R11, R12, R13",Resistor,RES SMD 10K OHM 1% 1/16W 0402,1276-3431-1-ND,,,,,,Samsung Electro-Mechanics,,RC1005F103CS
2,100k,RESISTOR0402_RES,0402_RES,"R14, R15",Resistor,RES SMD 100K OHM 1% 1/5W 0402,541-100KYCT-ND,,,,,,Vishay Dale,,CRCW0402100KFKEDHP
1,B3U-1000P,B3U-1000P,B3U-1000P,S1,Switch,SWITCH TACTILE SPST-NO 0.05A 12V,SW1020CT-ND,,,,,,Omron,,B3U-1000P
2,PTS645SM43SMTR92,PTS645SM43SMTR92,PTS645,"S2, S3",Tactile Switch SPST-NO Top Actuated Surface Mount,SWITCH TACTILE SPST-NO 0.05A 12V,CKN9112CT-ND,,,,,,C&K,,PTS645SM43SMTR92 LFS
1,TE_SSA12/SPDT,TE_SSA12/SPDT,TE_SSA12/SPDT,S4,SWITCH SLIDE SPDT 2POS SSA SER,SWITCH SLIDE SPDT 100MA 30V,450-1602-ND,,,,,,TE Connectivity ALCOSWITCH Switches,,SSA12
2,TEST_POINT_0.078IN,TEST_POINT_0.078IN,TESTPOINT_0.078IN,"TP40, TP41",Turret test point,TERM TURRET SINGLE L=4.75MM TIN,36-1520-2-ND,,,,,,Keystone Electronics,,1520-2
1,ADXL327,ADXL327,LFCSP-16,U1,ADXL327 3-Axis Analog Accelerometer,ACCELEROMETER 2G ANALOG 16LFCSP,ADXL327BCPZ-ND,,,,,,Analog Devices Inc.,,ADXL327BCPZ
1,MAX44009,MAX44009,UDFN-6-EXPOSED,U2,low power ambient light sensor,SENSOR AMBIENT LIGHT 6UTDFN,MAX44009EDT+TCT-ND,,,,,,Maxim Integrated,,MAX44009EDT+T
1,MPU-9250,MPU-9250,QFN-24/3MM,U3,GYRO/ACCEL/COMPASS/9-AXIS,IMU ACCEL/GYRO/MAG I2C/SPI 24QFN,1428-1019-1-ND,,,,,,TDK InvenSense,,MPU-9250
1,MS5637-02BA03,MS5637-02BA03,4-SMD,U4,low power pressure sensor,SENSOR 17.4PSIA I2C 24B 4-QFN,223-1199-1-ND,,,,,,TE CONNECTIVITY,,MS563702BA03-50
1,SI7021-A20-GM1,SI7021-A20-GM1,DFN-6/3MM,U5,IC TEMP SENSOR RH 2% DFN,SENS HUMI/TEMP 3.6V I2C 3% 6DFN,336-3141-ND,,,,,,Silicon Labs,634-SI7021-A20-GM1,SI7021-A20-GM1 
1,SIP32510,SIP32510,TSOT23-6,U6,"Load switch, slew rate controlled. By Vishay",IC LOAD SWITCH SOT23-6, SIP32510DT-T1-GE3CT-ND,,,,,,Vishay,,SIP32510DT-T1-GE3

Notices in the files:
parts and their libraries:
SparkFun-Aesthetics: Licensing: Creative Commons ShareAlike 4.0 International - https://creativecommons.org/licenses/by-sa/4.0
SparkFun-Connectors: Licensing: CC v3.0 Share-Alike You are welcome to use this library for commercial purposes.
